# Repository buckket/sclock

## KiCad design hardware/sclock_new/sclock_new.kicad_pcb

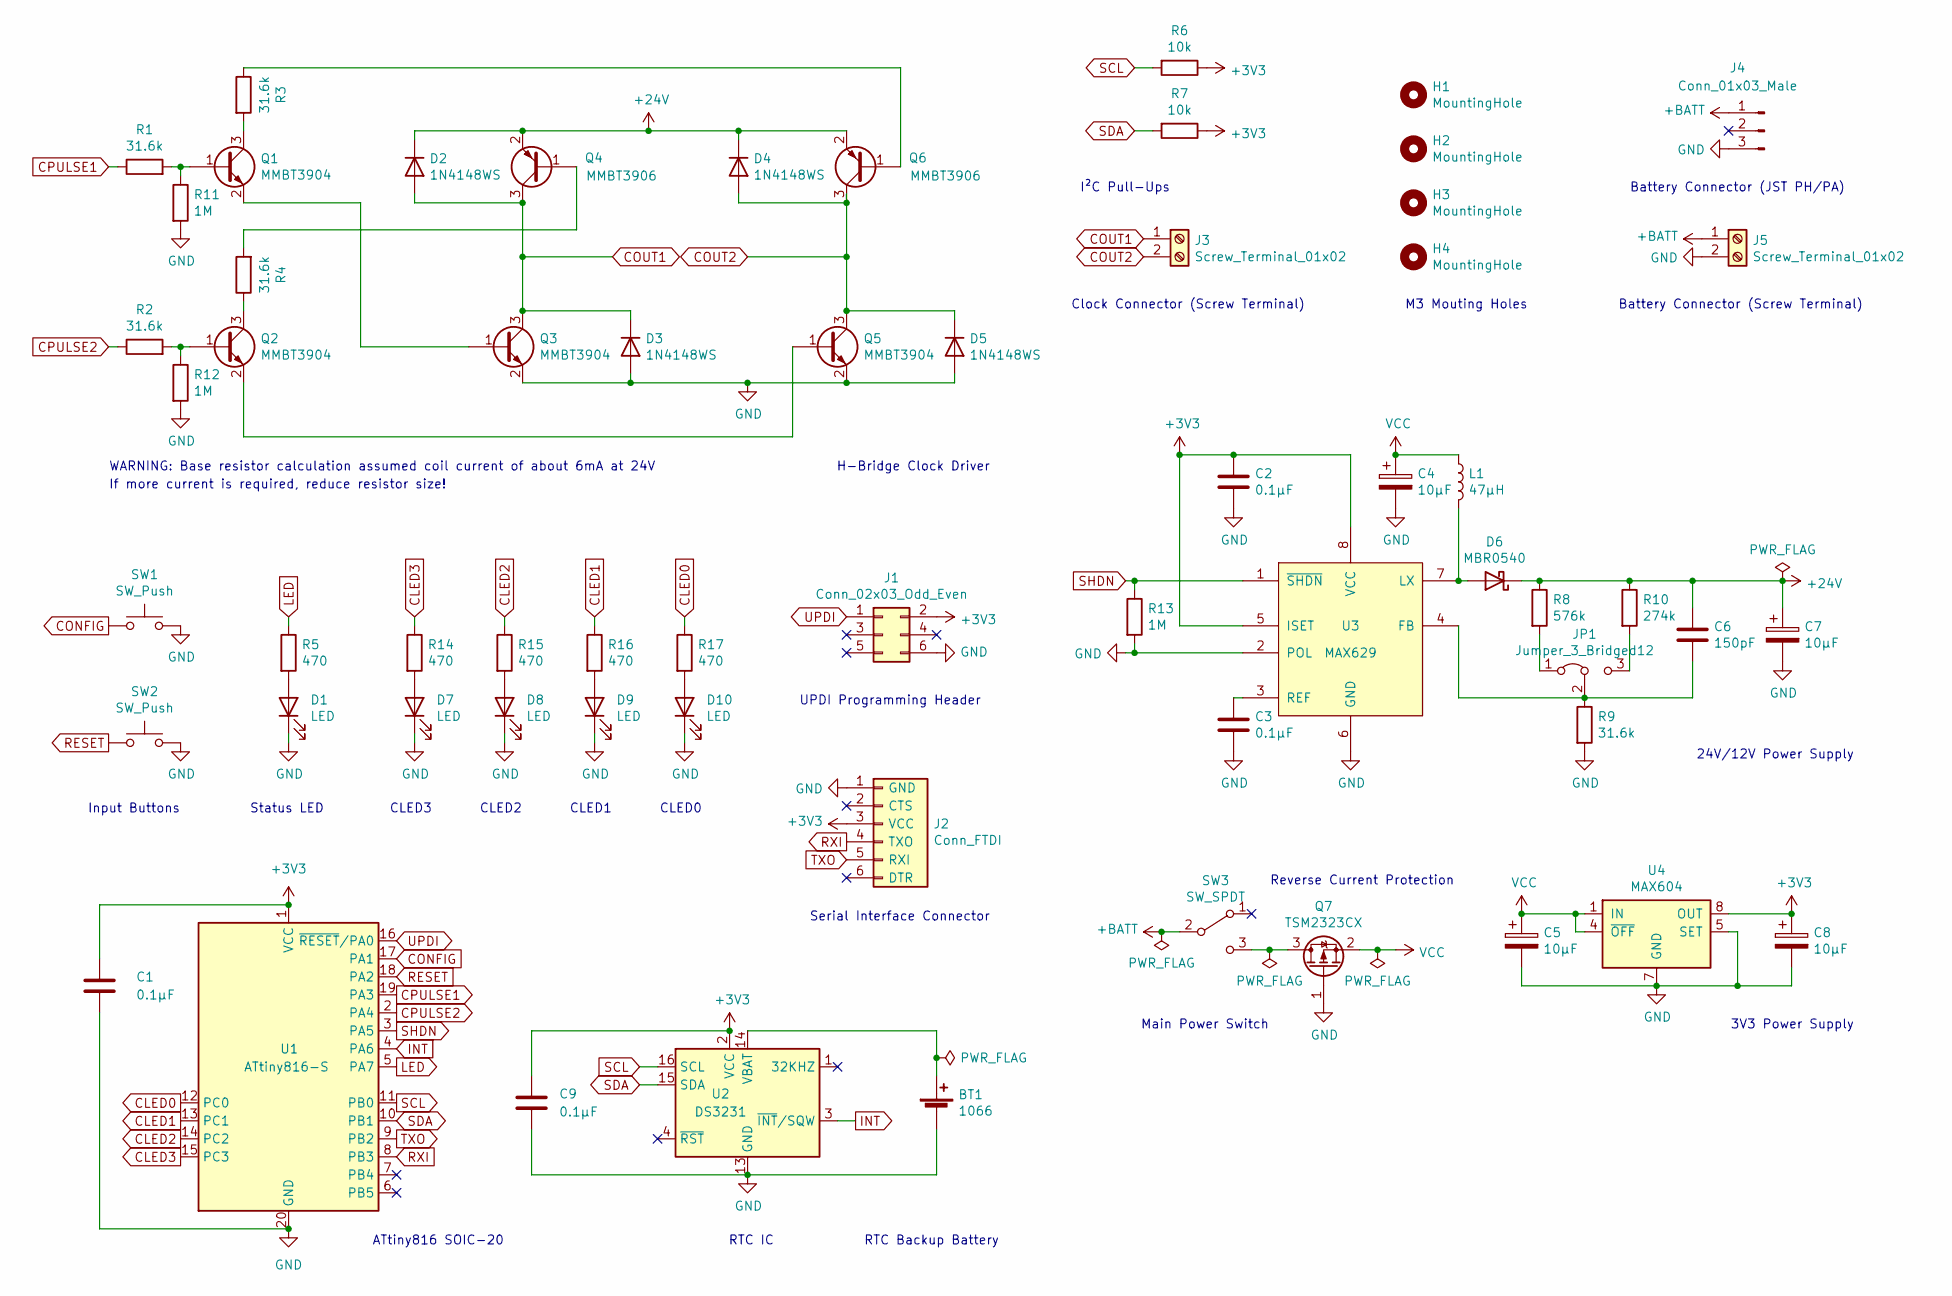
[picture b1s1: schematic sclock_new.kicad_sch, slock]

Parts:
BT1: 1066; BatteryHolder_Keystone_1066_1x2032; MPN 1066
C1, C2, C3, C9: 0.1µF; C_0805_2012Metric_Pad1.18x1.45mm_HandSolder; MPN C0805C104K5RACTU
C4, C7: 10µF; CP_EIA-7343-31_Kemet-D_Pad2.25x2.55mm_HandSolder; MPN T495D106K035ATE125
C5, C8: 10µF; CP_EIA-3216-18_Kemet-A_Pad1.58x1.35mm_HandSolder; MPN T494A106K010AT
C6: 150pF; C_0805_2012Metric_Pad1.18x1.45mm_HandSolder; MPN C0805C151J5GACTU
D1: LED; LED_0805_2012Metric_Pad1.15x1.40mm_HandSolder; MPN 150080VS75000
D2, D3, D4, D5: 1N4148WS; D_SOD-323_HandSoldering; MPN 1N4148WS
D6: MBR0540; D_SOD-123; MPN MBR0540T3G
D7, D8, D9, D10: LED; LED_0805_2012Metric_Pad1.15x1.40mm_HandSolder; MPN 150080YS75000
H1, H2, H3, H4: MountingHole; MountingHole_3.2mm_M3_Pad
J1: Conn_02x03_Odd_Even; PinHeader_2x03_P2.54mm_Vertical
J2: Conn_FTDI; PinHeader_1x06_P2.54mm_Horizontal
J3, J5: Screw_Terminal_01x02; TerminalBlock_4Ucon_1x02_P3.50mm_Horizontal; MPN 0393570002
J4: Conn_01x03_Male; JST_PH_B3B-PH-K_1x03_P2.00mm_Vertical
JP1: Jumper_3_Bridged12; PinHeader_1x03_P2.54mm_Vertical
L1: 47µH; L_Wuerth_WE-PD-Typ-LS_Handsoldering; MPN DR125-470-R
Q1, Q2, Q3, Q5: MMBT3904; SOT-23_Handsoldering; MPN MMBT3904LT1G
Q4, Q6: MMBT3906; SOT-23_Handsoldering; MPN MMBT3906LT1G
Q7: TSM2323CX; SOT-23_Handsoldering; MPN TSM2323CX RFG
R1, R2, R3, R4, R9: 31.6k; R_0805_2012Metric_Pad1.20x1.40mm_HandSolder; MPN RC0805FR-0731K6L
R5, R14, R15, R16, R17: 470; R_0805_2012Metric_Pad1.20x1.40mm_HandSolder; MPN RC0805FR-07470RL
R6, R7: 10k; R_0805_2012Metric_Pad1.20x1.40mm_HandSolder; MPN RC0805FR-0710KL
R8: 576k; R_0805_2012Metric_Pad1.20x1.40mm_HandSolder; MPN RC0805FR-07576KL
R10: 274k; R_0805_2012Metric_Pad1.20x1.40mm_HandSolder; MPN RC0805FR-07274KL
R11, R12, R13: 1M; R_0805_2012Metric_Pad1.20x1.40mm_HandSolder; MPN RC0805FR-071ML
SW1, SW2: SW_Push; SW_SPST_TL3342; MPN TL3342F160QG/TR
SW3: SW_SPDT; SW_E-Switch_EG1271_DPDT; MPN EG1271
U1: ATtiny816-S; SOIC-20W_7.5x12.8mm_P1.27mm; MPN ATTINY816-SFR
U2: DS3231; SOIC-16W_7.5x10.3mm_P1.27mm; MPN DS3231S#T&R
U3: MAX629; SOIC-8_3.9x4.9mm_P1.27mm; MPN MAX629ESA+
U4: MAX604; SOIC-8_3.9x4.9mm_P1.27mm; MPN MAX604ESA+

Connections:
+3V3: C1.1, C2.1, C8.1, C9.1, J1.2, J2.3 (VCC), R6.1, R7.1, U1.1 (VCC), U2.2 (VCC), U3.5 (ISET), U3.8 (VCC), U4.8 (OUT)
+24V: C6.1, C7.1, D2.1 (K), D4.1 (K), D6.1 (K), Q4.2 (E), Q6.2 (E), R8.1, R10.1
+BATT: J4.1, J5.1, SW3.2 (B)
CLED0: R17.1, U1.12 (PC0)
CLED1: R16.1, U1.13 (PC1)
CLED2: R15.1, U1.14 (PC2)
CLED3: R14.1, U1.15 (PC3)
CONFIG: SW1.1, U1.17 (PA1)
COUT1: D2.2 (A), D3.1 (K), J3.1, Q3.3 (C), Q4.3 (C)
COUT2: D4.2 (A), D5.1 (K), J3.2, Q5.3 (C), Q6.3 (C)
CPULSE1: R1.1, U1.19 (PA3)
CPULSE2: R2.1, U1.2 (PA4)
GND: BT1.2 (-), C1.2, C2.2, C3.2, C4.2, C5.2, C7.2, C8.2, C9.2, D1.1 (K), D3.2 (A), D5.2 (A), D7.1 (K), D8.1 (K), D9.1 (K), D10.1 (K), J1.6, J2.1 (GND), J4.3, J5.2, Q3.2 (E), Q5.2 (E), Q7.1 (G), R9.2, R11.2, R12.2, R13.2, SW1.2, SW2.2, U1.20 (GND), U2.5 (GND), U2.6 (GND), U2.7 (GND), U2.8 (GND), U2.9 (GND), U2.10 (GND), U2.11 (GND), U2.12 (GND), U2.13 (GND), U3.2 (POL), U3.6 (GND), U4.2 (GND), U4.3 (GND), U4.5 (SET), U4.6 (GND), U4.7 (GND)
INT: U1.4 (PA6), U2.3 (~INT/SQW)
LED: R5.1, U1.5 (PA7)
unnamed: BT1.1 (+), U2.14 (VBAT)
unnamed: C3.1, U3.3 (REF)
unnamed: C6.2, JP1.2 (C), R9.1, U3.4 (FB)
unnamed: D1.2 (A), R5.2
unnamed: D6.2 (A), L1.2, U3.7 (LX)
unnamed: D7.2 (A), R14.2
unnamed: D8.2 (A), R15.2
unnamed: D9.2 (A), R16.2
unnamed: D10.2 (A), R17.2
unnamed: JP1.1 (A), R8.2
unnamed: JP1.3 (B), R10.2
unnamed: Q1.1 (B), R1.2, R11.1
unnamed: Q1.2 (E), Q3.1 (B)
unnamed: Q1.3 (C), R3.2
unnamed: Q2.1 (B), R2.2, R12.1
unnamed: Q2.2 (E), Q5.1 (B)
unnamed: Q2.3 (C), R4.1
unnamed: Q4.1 (B), R4.2
unnamed: Q6.1 (B), R3.1
unnamed: Q7.3 (D), SW3.3 (C)
RESET: SW2.1, U1.18 (PA2)
RXI: J2.4 (TXO), U1.8 (PB3)
SCL: R6.2, U1.11 (PB0), U2.16 (SCL)
SDA: R7.2, U1.10 (PB1), U2.15 (SDA)
SHDN: R13.1, U1.3 (PA5), U3.1 (~SHDN)
TXO: J2.5 (RXI), U1.9 (PB2)
UPDI: J1.1, U1.16 (~RESET/PA0)
VCC: C4.1, C5.1, L1.1, Q7.2 (S), U4.1 (IN), U4.4 (~OFF)

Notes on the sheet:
M3 Mouting Holes
RTC Backup Battery
ATtiny816 SOIC-20
Battery Connector (JST PH/PA)
Reverse Current Protection
RTC IC
UPDI Programming Header
CLED2
CLED3
Main Power Switch
WARNING: Base resistor calculation assumed coil current of about 6mA at 24V
Clock Connector (Screw Terminal)
Battery Connector (Screw Terminal)
3V3 Power Supply
Status LED
24V/12V Power Supply
CLED0
H-Bridge Clock Driver
I²C Pull-Ups
Serial Interface Connector
If more current is required, reduce resistor size!
Input Buttons
CLED1

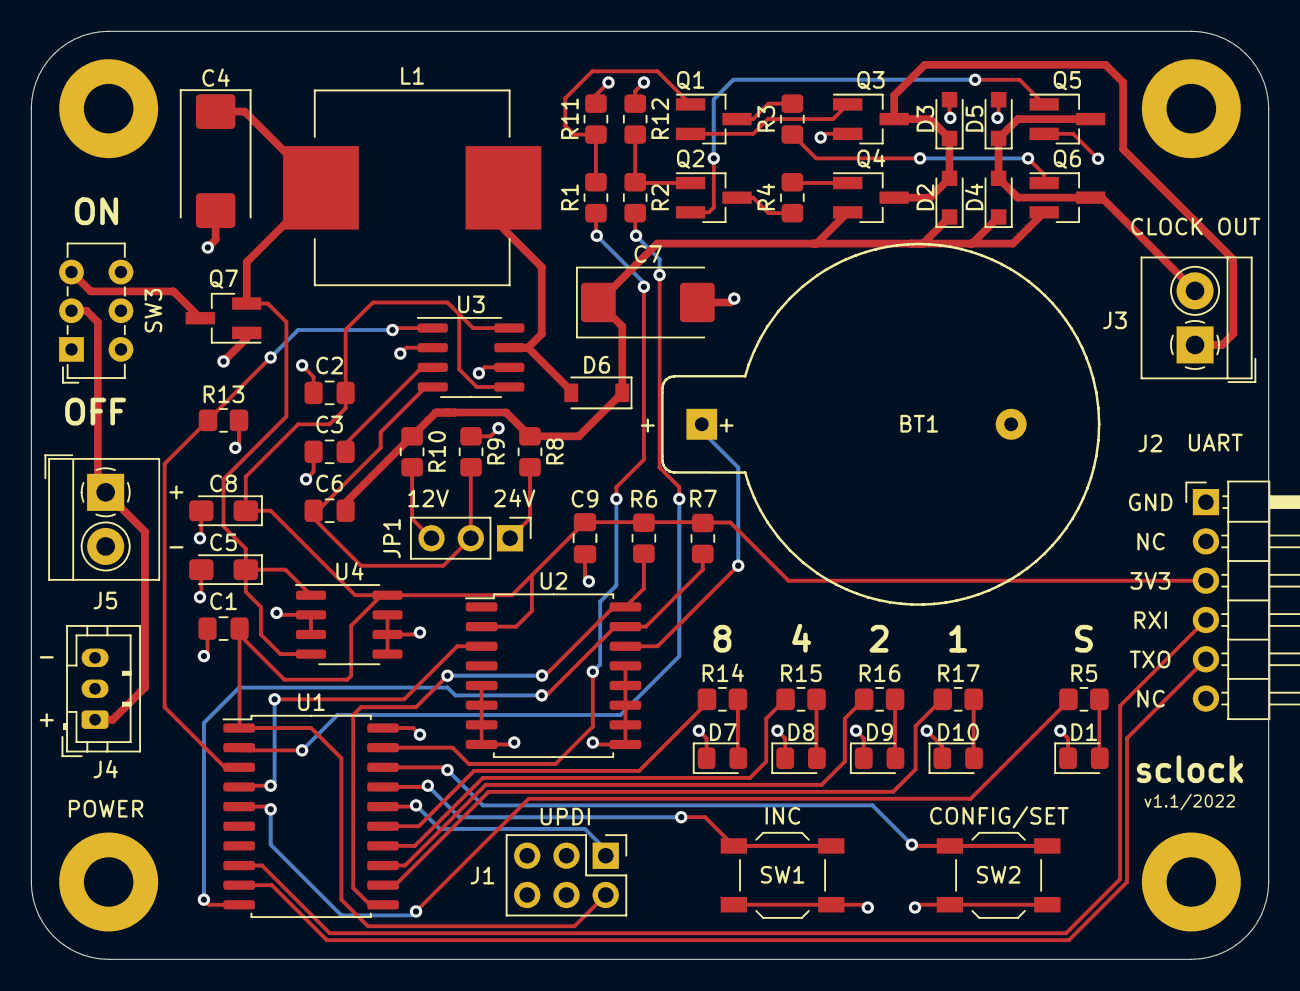
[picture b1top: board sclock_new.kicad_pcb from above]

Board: 2 copper layers, 80.0 x 60.0 mm, 62 parts (0 on the bottom side), 43 nets.

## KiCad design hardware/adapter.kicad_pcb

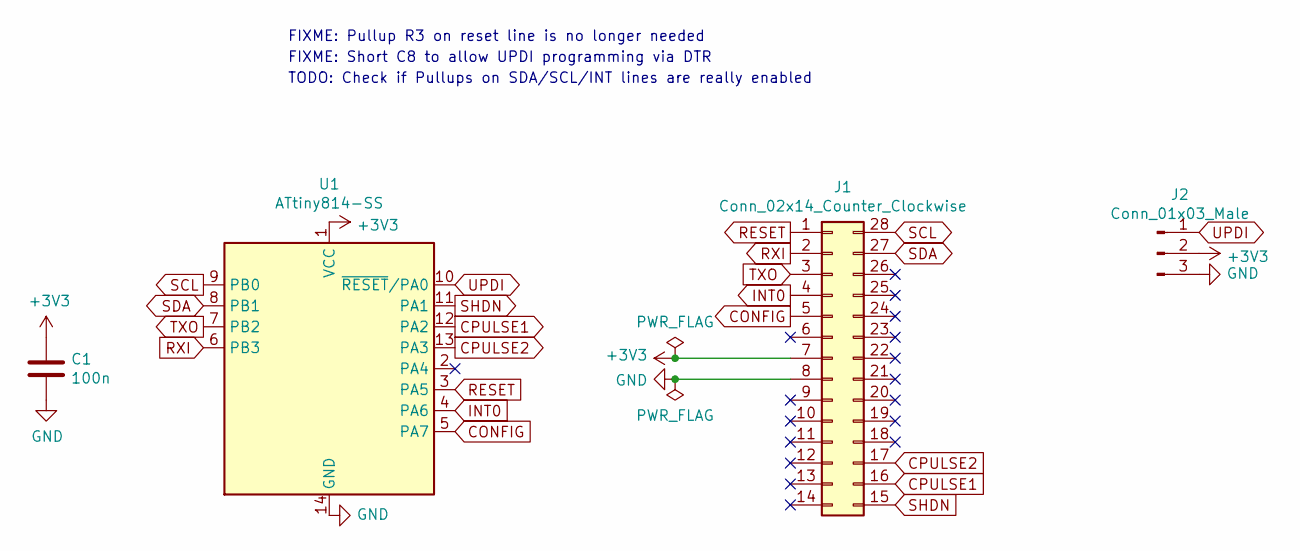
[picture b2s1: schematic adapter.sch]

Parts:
C1: 100n; C_0805_2012Metric_Pad1.18x1.45mm_HandSolder
J1: Conn_02x14_Counter_Clockwise; DIP-28_W7.62mm
J2: Conn_01x03_Male; PinSocket_1x03_P2.54mm_Vertical
U1: ATtiny814-SS; SOIC-14_3.9x8.7mm_P1.27mm

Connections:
+3V3: C1.1, J1.7, J2.2, U1.1 (VCC)
CONFIG: J1.5, U1.5 (PA7)
CPULSE1: J1.16, U1.12 (PA2)
CPULSE2: J1.17, U1.13 (PA3)
GND: C1.2, J1.8, J2.3, U1.14 (GND)
INT0: J1.4, U1.4 (PA6)
RESET: J1.1, U1.3 (PA5)
RXI: J1.2, U1.6 (PB3)
SCL: J1.28, U1.9 (PB0)
SDA: J1.27, U1.8 (PB1)
SHDN: J1.15, U1.11 (PA1)
TXO: J1.3, U1.7 (PB2)
UPDI: J2.1, U1.10 (~RESET~/PA0)

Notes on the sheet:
FIXME: Pullup R3 on reset line is no longer needed
FIXME: Short C8 to allow UPDI programming via DTR
TODO: Check if Pullups on SDA/SCL/INT lines are really enabled

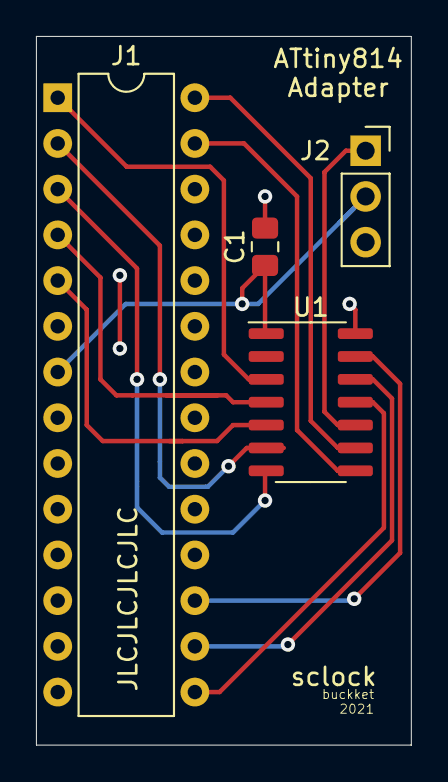
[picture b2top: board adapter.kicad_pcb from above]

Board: 2 copper layers, 20.8 x 39.4 mm, 4 parts (0 on the bottom side), 13 nets.

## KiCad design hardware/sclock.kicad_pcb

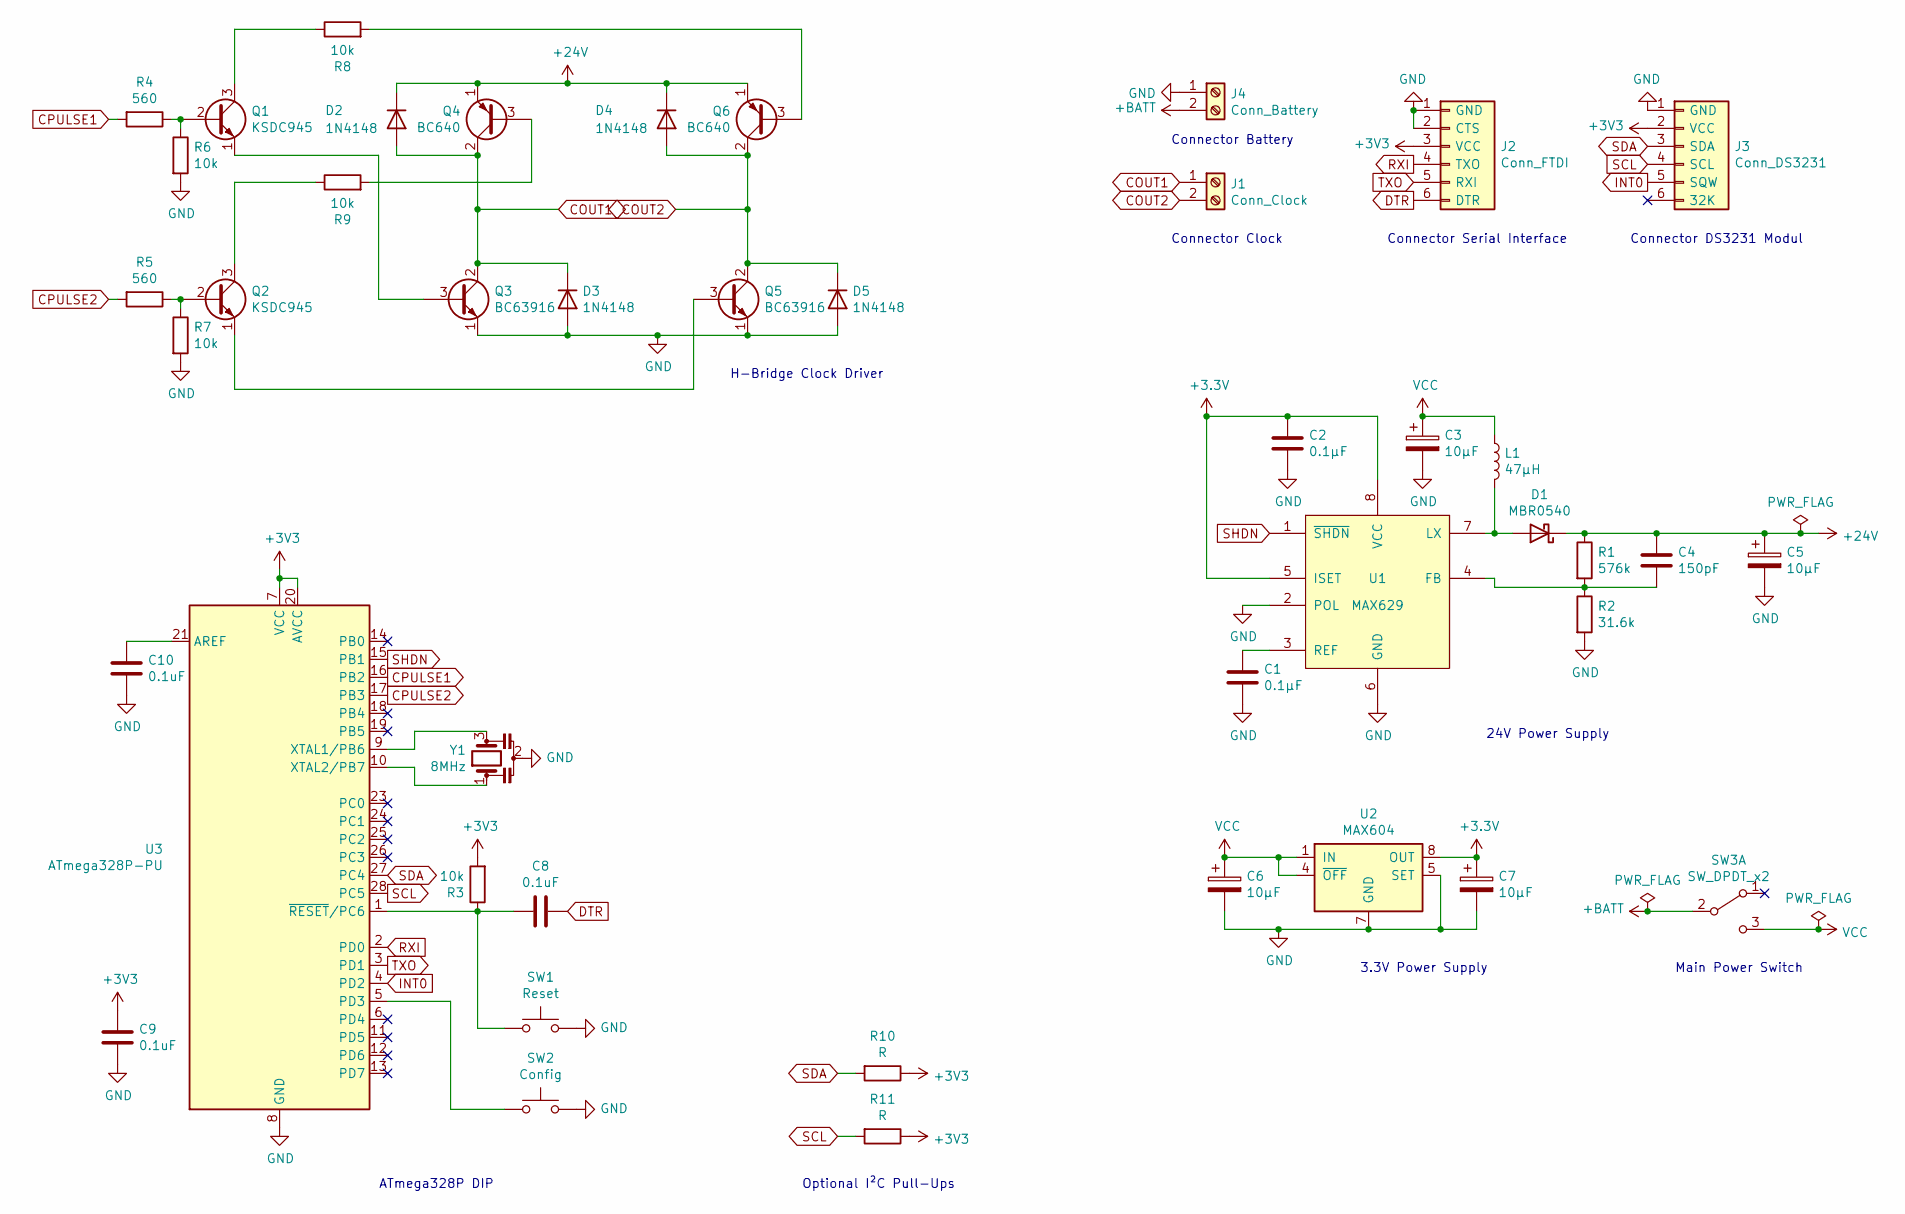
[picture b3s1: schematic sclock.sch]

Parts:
C1, C2: 0.1µF; C_0805_2012Metric_Pad1.15x1.40mm_HandSolder
C3, C5, C6, C7: 10µF; CP_Radial_D5.0mm_P2.00mm
C4: 150pF; C_0805_2012Metric_Pad1.15x1.40mm_HandSolder
C8, C9, C10: 0.1uF; C_0805_2012Metric_Pad1.15x1.40mm_HandSolder
D1: MBR0540; D_SOD-123
D2, D3, D4, D5: 1N4148; D_DO-35_SOD27_P7.62mm_Horizontal
J1: Conn_Clock; TerminalBlock_4Ucon_1x02_P3.50mm_Horizontal
J2: Conn_FTDI; PinHeader_1x06_P2.54mm_Vertical
J3: Conn_DS3231; PinHeader_1x06_P2.54mm_Horizontal
J4: Conn_Battery; TerminalBlock_4Ucon_1x02_P3.50mm_Horizontal
L1: 47µH; L_Wuerth_WE-PD-Typ-LS_Handsoldering
Q1, Q2: KSDC945; TO-92
Q3, Q5: BC63916; TO-92
Q4, Q6: BC640; TO-92
R1: 576k; R_0805_2012Metric_Pad1.15x1.40mm_HandSolder
R2: 31.6k; R_0805_2012Metric_Pad1.15x1.40mm_HandSolder
R3, R6, R7, R8, R9: 10k; R_0805_2012Metric_Pad1.15x1.40mm_HandSolder
R4, R5: 560; R_0805_2012Metric_Pad1.15x1.40mm_HandSolder
R10, R11: R; R_0805_2012Metric_Pad1.15x1.40mm_HandSolder
SW1: Reset; SW_PUSH_6mm
SW2: Config; SW_PUSH_6mm
SW3: SW_DPDT_x2; Slide_Switch_DPDT
U1: MAX629; SOIC-8_3.9x4.9mm_P1.27mm
U2: MAX604; SOIC-8_3.9x4.9mm_P1.27mm
U3: ATmega328P-PU; DIP-28_W7.62mm
Y1: 8MHz; Resonator_SMD_muRata_SFECV-3Pin_6.9x2.9mm_HandSoldering

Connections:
+24V: C4.1, C5.1, D1.1 (K), D2.1 (K), D4.1 (K), Q4.1 (E), Q6.1 (E), R1.1
+BATT: J4.2, SW3.2 (B); also elsewhere on the board
COUT1: D2.2 (A), D3.1 (K), J1.1, Q3.2 (C), Q4.2 (C); also elsewhere on the board
COUT2: D4.2 (A), D5.1 (K), J1.2, Q5.2 (C), Q6.2 (C); also elsewhere on the board
CPULSE1: R4.2, U3.16 (PB2)
CPULSE2: R5.2, U3.17 (PB3)
DTR: C8.2, J2.6 (DTR); also elsewhere on the board
GND: C1.2, C2.2, C3.2, C5.2, C6.2, C7.2, C9.2, C10.2, D3.2 (A), D5.2 (A), J2.1 (GND), J2.2 (CTS), J3.1 (GND), J4.1, Q3.1 (E), Q5.1 (E), R2.2, R6.2, R7.2, SW1.2, SW2.2, U1.2 (POL), U1.6 (GND), U2.2 (GND), U2.3 (GND), U2.5 (SET), U2.6 (GND), U2.7 (GND), U3.8 (GND), U3.22 (GND), Y1.2; also elsewhere on the board
INT0: J3.5 (SQW), U3.4 (PD2); also elsewhere on the board
unnamed: C1.1, U1.3 (REF)
unnamed: C4.2, R1.2, R2.1, U1.4 (FB)
unnamed: C8.1, R3.1, SW1.1, U3.1 (~RESET~/PC6)
unnamed: C10.1, U3.21 (AREF)
unnamed: D1.2 (A), L1.2, U1.7 (LX)
unnamed: Q1.1 (E), Q3.3 (B)
unnamed: Q1.2 (B), R4.1, R6.1
unnamed: Q1.3 (C), R8.1
unnamed: Q2.1 (E), Q5.3 (B)
unnamed: Q2.2 (B), R5.1, R7.1
unnamed: Q2.3 (C), R9.1
unnamed: Q4.3 (B), R9.2
unnamed: Q6.3 (B), R8.2
unnamed: SW2.1, U3.5 (PD3)
unnamed: U3.9 (XTAL1/PB6), Y1.3
unnamed: U3.10 (XTAL2/PB7), Y1.1
RXI: J2.4 (TXO), U3.2 (PD0); also elsewhere on the board
SCL: J3.4 (SCL), R11.2, U3.28 (PC5); also elsewhere on the board
SDA: J3.3 (SDA), R10.2, U3.27 (PC4); also elsewhere on the board
SHDN: U1.1 (~SHDN), U3.15 (PB1)
TXO: J2.5 (RXI), U3.3 (PD1); also elsewhere on the board
VCC: C3.1, C6.1, L1.1, SW3.3 (C), U2.1 (IN), U2.4 (~OFF)

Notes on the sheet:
24V Power Supply
Optional I²C Pull-Ups
ATmega328P DIP
Main Power Switch
3.3V Power Supply
H-Bridge Clock Driver
Connector DS3231 Modul
Connector Serial Interface
Connector Clock
Connector Battery

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
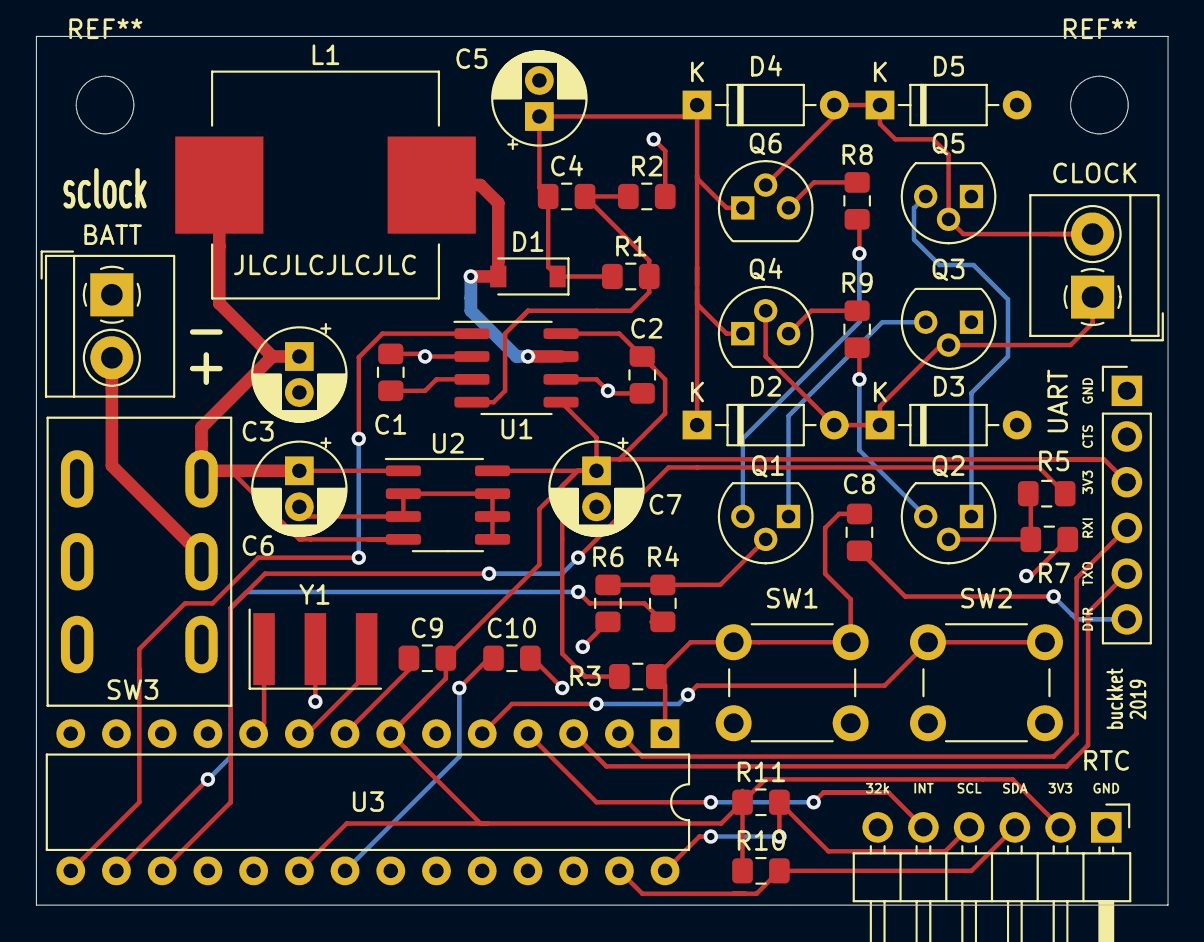
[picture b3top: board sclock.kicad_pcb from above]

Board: 2 copper layers, 62.9 x 48.3 mm, 44 parts (0 on the bottom side), 32 nets.

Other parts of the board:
BATT: Conn_Battery; TerminalBlock_4Ucon_1x02_P3.50mm_Horizontal
CLOCK: Conn_Clock; TerminalBlock_4Ucon_1x02_P3.50mm_Horizontal
RTC: Conn_DS3231; PinHeader_1x06_P2.54mm_Horizontal
UART: Conn_FTDI; PinHeader_1x06_P2.54mm_Vertical

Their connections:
+BATT: BATT.2; also elsewhere on the board
COUT1: CLOCK.1; also elsewhere on the board
COUT2: CLOCK.2; also elsewhere on the board
DTR: UART.6; also elsewhere on the board
GND: BATT.1, RTC.1, UART.1, UART.2; also elsewhere on the board
INT0: RTC.5; also elsewhere on the board
RXI: UART.4; also elsewhere on the board
SCL: RTC.4; also elsewhere on the board
SDA: RTC.3; also elsewhere on the board
TXO: UART.5; also elsewhere on the board

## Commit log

2021-03-05 Update sclock
2021-03-06 PCB for ATmega328
2021-03-06 Add adapter PCB, reorganize files
2021-03-06 Add source code for ATtiny814
2021-03-06 Reformat ATtiny source
2021-03-11 Update sclock_tiny
2021-03-26 Add Keystone 1066 battery holder footprint and 3D model
2021-03-26 New PCB dev state
2021-03-30 Fix inline function problem in clock.h
2021-03-30 Add platformio.ini for attiny
2021-03-30 Add .gitlab-ci.yml
2021-03-30 Remove .travis.yml
2021-03-30 dos2unix
2021-11-05 New PCB changes
2022-11-19 PCB v1.1
